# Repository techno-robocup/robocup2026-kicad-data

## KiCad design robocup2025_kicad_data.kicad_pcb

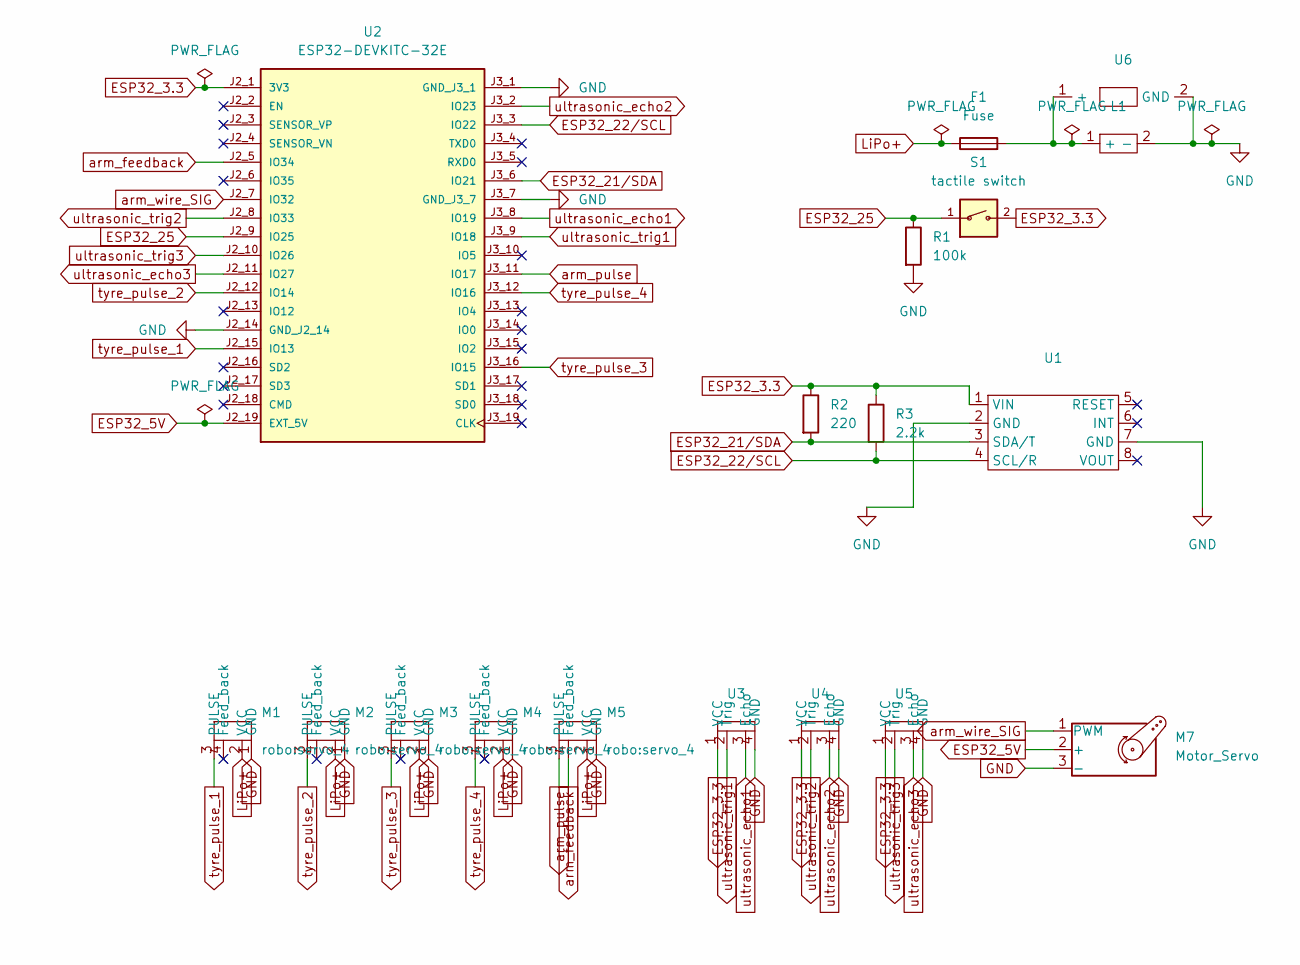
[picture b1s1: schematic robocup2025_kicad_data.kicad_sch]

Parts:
F1: Fuse; fuse_holder
L1: LiPo
M1, M2, M3, M4, M5: servo_4
M7: Motor_Servo; servo_motor_3
R1: 100k; R_Axial_DIN0204_L3.6mm_D1.6mm_P7.62mm_Horizontal
R2: 220; R_Axial_DIN0204_L3.6mm_D1.6mm_P7.62mm_Horizontal
R3: 2.2k; R_Axial_DIN0204_L3.6mm_D1.6mm_P7.62mm_Horizontal
S1: tactile switch; DS-850K-S-ON; PARTREV P6
U1: AE-BNO055-BO
U2: ESP32-DEVKITC-32E; MODULE_ESP32-DEVKITC-32E; PARTREV 1.4
U3, U4, U5: ultrasonic
U6: voltmeter

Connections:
ESP32_3.3: R2.1, R3.1, S1.2, U1.1 (VIN), U2.J2_1 (3V3), U3.1 (VCC), U4.1 (VCC), U5.1 (VCC)
ESP32_5V: M7.2 (+), U2.J2_19 (EXT_5V)
ESP32_21/SDA: R2.2, U1.3 (SDA/T), U2.J3_6 (IO21)
ESP32_22/SCL: R3.2, U1.4 (SCL/R), U2.J3_3 (IO22)
ESP32_25: R1.1, S1.1, U2.J2_9 (IO25)
GND: L1.2 (-), M1.1 (GND), M2.1 (GND), M3.1 (GND), M4.1 (GND), M5.1 (GND), M7.3 (-), R1.2, U1.2 (GND), U1.7 (GND), U2.J2_14 (GND_J2_14), U2.J3_1 (GND_J3_1), U2.J3_7 (GND_J3_7), U3.4 (GND), U4.4 (GND), U5.4 (GND), U6.2 (GND)
LiPo+: F1.1, M1.2 (VCC), M2.2 (VCC), M3.2 (VCC), M4.2 (VCC), M5.2 (VCC)
unnamed: F1.2, L1.1 (+), U6.1 (+)
arm_feedback: M5.4 (Feed_back), U2.J2_5 (IO34)
arm_pulse: M5.3 (PULSE), U2.J3_11 (IO17)
arm_wire_SIG: M7.1 (PWM), U2.J2_7 (IO32)
tyre_pulse_1: M1.3 (PULSE), U2.J2_15 (IO13)
tyre_pulse_2: M2.3 (PULSE), U2.J2_12 (IO14)
tyre_pulse_3: M3.3 (PULSE), U2.J3_16 (IO15)
tyre_pulse_4: M4.3 (PULSE), U2.J3_12 (IO16)
ultrasonic_echo1: U2.J3_8 (IO19), U3.3 (Echo)
ultrasonic_echo2: U2.J3_2 (IO23), U4.3 (Echo)
ultrasonic_echo3: U2.J2_11 (IO27), U5.3 (Echo)
ultrasonic_trig1: U2.J3_9 (IO18), U3.2 (Trig)
ultrasonic_trig2: U2.J2_8 (IO33), U4.2 (Trig)
ultrasonic_trig3: U2.J2_10 (IO26), U5.2 (Trig)

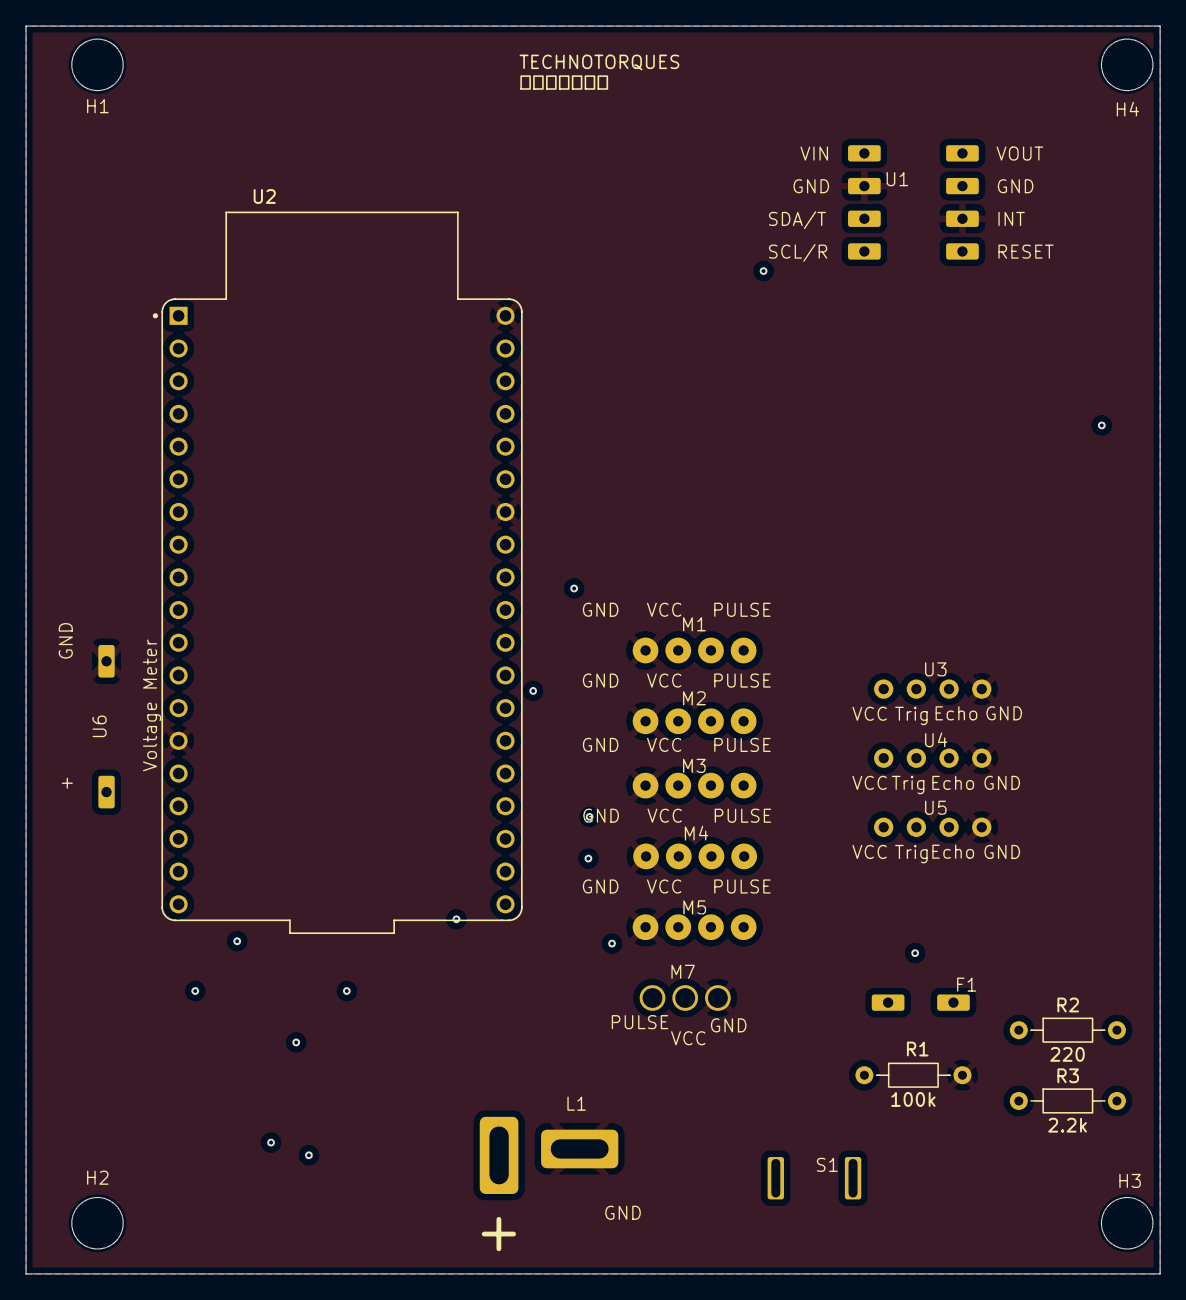
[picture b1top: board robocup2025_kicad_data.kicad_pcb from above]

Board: 4 copper layers, 88.1 x 96.9 mm, 22 parts (0 on the bottom side), 21 nets.

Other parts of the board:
H1, H2, H3, H4: 4mm diameter through hole

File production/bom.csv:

Designator,Footprint,Quantity,Value,LCSC Part #
F1,fuse_holder,1,Fuse,
"H1, H2, H3, H4",4mm diameter through hole,4,4mm diameter through hole,
L1,LiPo,1,~,
"M1, M2, M3, M4, M5",servo_4,5,~,
M7,servo_motor_3,1,Motor_Servo,
R1,R_Axial_DIN0204_L3.6mm_D1.6mm_P7.62mm_Horizontal,1,100k,
R2,R_Axial_DIN0204_L3.6mm_D1.6mm_P7.62mm_Horizontal,1,220,
R3,R_Axial_DIN0204_L3.6mm_D1.6mm_P7.62mm_Horizontal,1,2.2k,
S1,DS-850K-S-ON,1,tactile switch,
U1,AE-BNO055-BO,1,~,
U2,MODULE_ESP32-DEVKITC-32E,1,ESP32-DEVKITC-32E,
"U3, U4, U5",ultrasonic,3,~,
U6,voltmeter,1,~,

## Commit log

2026-01-12 fixed wrong power flags
2026-01-14 new schematics and pcbs
2026-01-14 adding routed pcb
2026-01-14 modified
2026-01-14 new fabrication data
